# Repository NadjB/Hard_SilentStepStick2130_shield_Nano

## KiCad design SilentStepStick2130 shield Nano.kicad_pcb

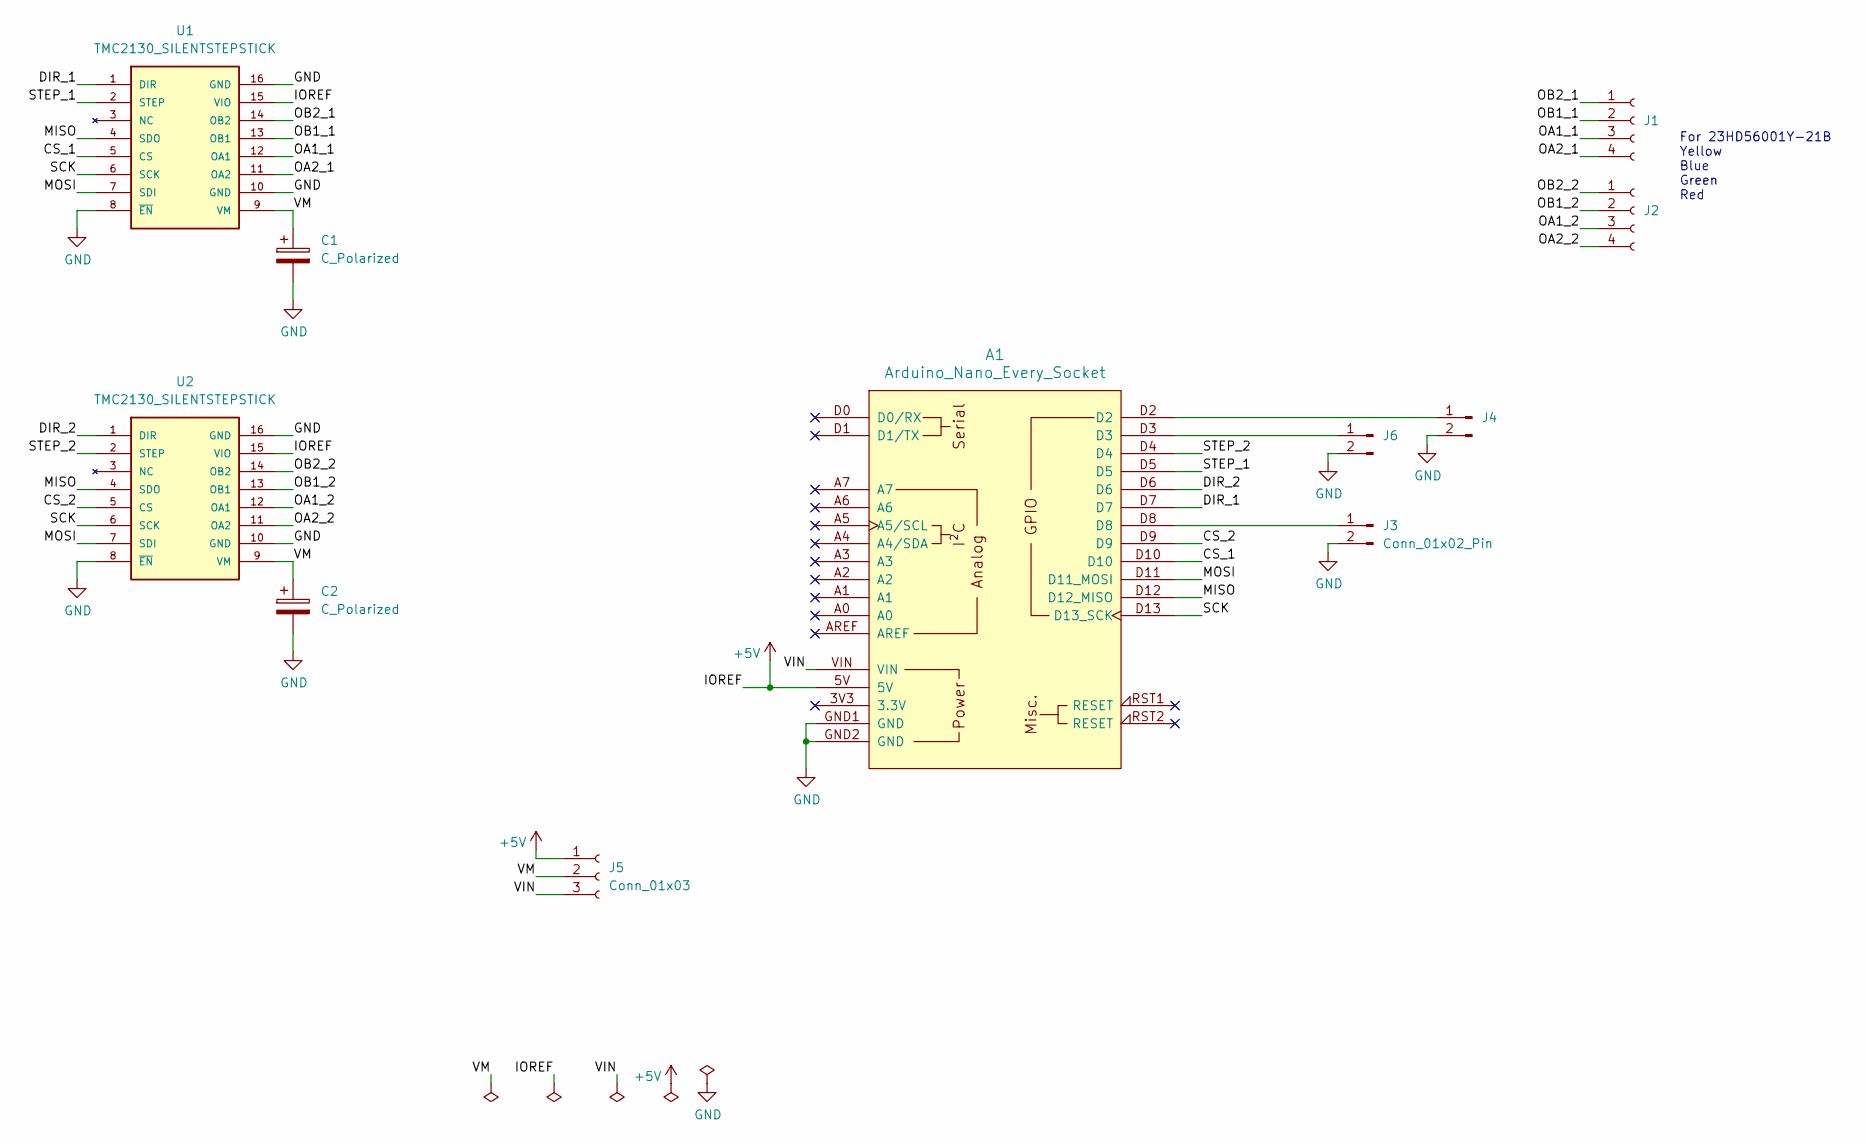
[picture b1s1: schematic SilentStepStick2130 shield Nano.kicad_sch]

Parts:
A1: Arduino_Nano_Every_Socket
C1, C2: C_Polarized; CP_EIA-7343-43_Kemet-X_Pad2.25x2.55mm_HandSolder
J1, J2: Conn_01x04_Socket; CUI_TBL009-254-04BK-2OR
J3, J4, J6: Conn_01x02_Pin; JST_XA_S02B-XASK-1_1x02_P2.50mm_Horizontal
J5: Conn_01x03; PinHeader_1x03_P2.54mm_Vertical; Part Number 1-0301FBV0T
U1, U2: TMC2130_SILENTSTEPSTICK

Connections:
+5V: A1.5V, J5.1, U1.15 (VIO), U2.15 (VIO)
/CS_1: A1.D10, U1.5 (CS)
/CS_2: A1.D9, U2.5 (CS)
/DIR_1: A1.D7, U1.1 (DIR)
/DIR_2: A1.D6, U2.1 (DIR)
/MISO: A1.D12 (D12_MISO), U1.4 (SDO), U2.4 (SDO)
/MOSI: A1.D11 (D11_MOSI), U1.7 (SDI), U2.7 (SDI)
/OA1_1: J1.3, U1.12 (OA1)
/OA1_2: J2.3, U2.12 (OA1)
/OA2_1: J1.4, U1.11 (OA2)
/OA2_2: J2.4, U2.11 (OA2)
/OB1_1: J1.2, U1.13 (OB1)
/OB1_2: J2.2, U2.13 (OB1)
/OB2_1: J1.1, U1.14 (OB2)
/OB2_2: J2.1, U2.14 (OB2)
/SCK: A1.D13 (D13_SCK), U1.6 (SCK), U2.6 (SCK)
/STEP_1: A1.D5, U1.2 (STEP)
/STEP_2: A1.D4, U2.2 (STEP)
/VIN: A1.VIN, J5.3
/VM: C1.1, C2.1, J5.2, U1.9 (VM), U2.9 (VM)
GND: A1.GND1 (GND), A1.GND2 (GND), C1.2, C2.2, J3.2, J4.2, J6.2, U1.8 (~EN), U1.10 (GND), U1.16 (GND), U2.8 (~EN), U2.10 (GND), U2.16 (GND)
unnamed: A1.D8, J3.1
unnamed: A1.D2, J4.1
unnamed: A1.D3, J6.1

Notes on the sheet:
For 23HD56001Y-21B Yellow Blue Green Red

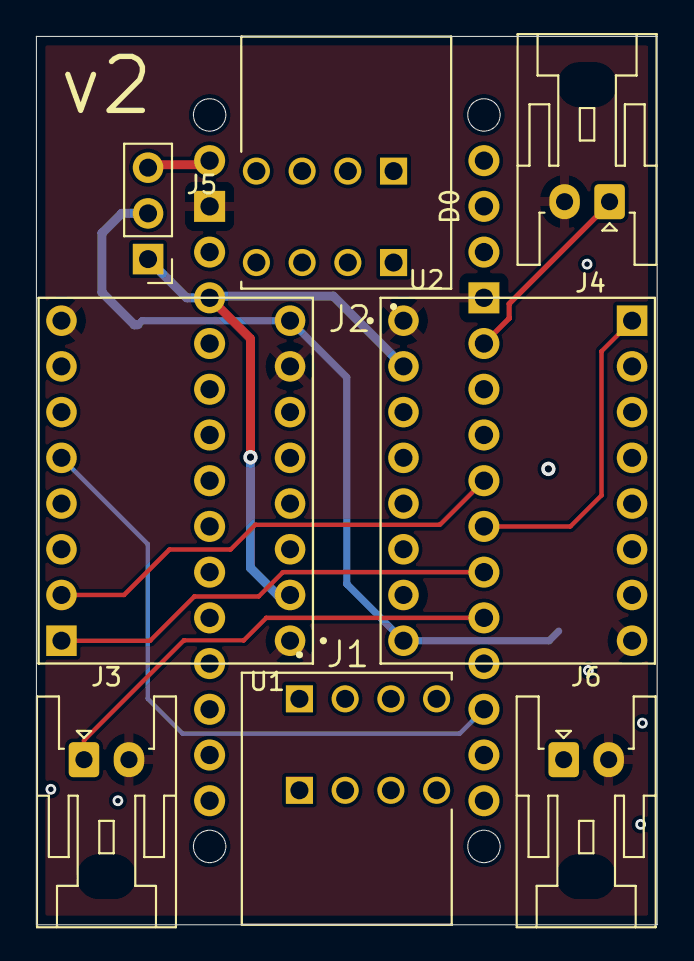
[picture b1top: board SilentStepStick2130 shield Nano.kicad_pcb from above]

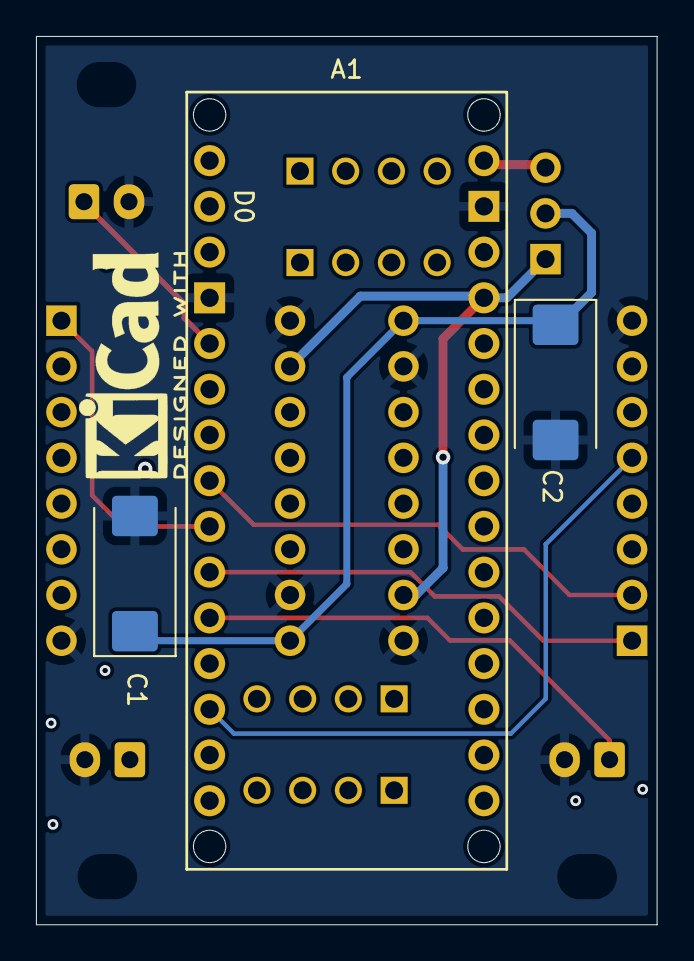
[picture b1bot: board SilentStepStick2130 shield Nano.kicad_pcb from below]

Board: 4 copper layers, 34.5 x 49.4 mm, 11 parts (3 on the bottom side), 24 nets.

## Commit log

2024-03-15 V0 sent to prod
2025-04-03 redo, nano on the wrong side (can work with headerless nano)
